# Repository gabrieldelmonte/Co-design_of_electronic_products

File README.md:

# PBLE01 - Electronic Product Co-design Project

## Overview
This repository contains the complete design files and documentation for PBLE01 - Electronic Product Co-design, a university project developed at UNIFEI (Federal University of Itajubá). The project involves designing a custom printed circuit board (PCB) with microcontroller-based functionality, peripheral interfaces, and power management systems.

## Project Features
- **Microcontroller**: STM32F030K6T6TR (ARM Cortex-M0)
- **Power Supply**: 5V via USB-C with voltage regulation to 3.3V
- **Peripherals**:
  - LCD interface (16x2 character display)
  - 3-button tactile keyboard
  - Status LEDs
  - USB-Serial transceiver (MCP2200)
  - EEPROM memory (24LC512)
  - Light sensor (PDV-P8103 photoresistor)
- **Expansion Interfaces**:
  - SPI connector
  - I²C connector
  - General-purpose GPIO pins
- **Programming Interfaces**: SWD and UART
- **Safety Features**:
  - Overcurrent protection (PPTC fuse)
  - Reverse voltage protection
  - Power indication LEDs

## Technical Specifications
| Parameter             | Value               |
|-----------------------|---------------------|
| PCB Dimensions        | 70 × 70 mm          |
| Layer Count           | 2 (double-sided)    |
| Signal Trace Width    | ≥ 8 mils            |
| Power Trace Width     | ≥ 12 mils           |
| Minimum Spacing       | 8 mils              |
| Minimum Via Diameter  | 12 mils             |
| Operating Voltage     | 5V DC (USB powered) |
| Voltage Regulation    | 3.3V (LD1117S33TR)  |
| Microcontroller Clock | 8 MHz crystal       |

## Repository Structure

```
├── Hardware/
│   └── Projeto_2022014552/ # Complete KiCad design files
├── Documentation/
│   ├── Manual.pdf          # Complete technical documentation
│   ├── Design_Guidelines.pdf
│   └── Requirements.pdf
└── Components/
    └── .../                # Components used in the project Kicad
```

## Design Tools
- **PCB Design**: KiCad v8.99
- **Documentation**: LaTeX/Overleaf
- **Simulation**: Not applicable (hardware-only project)

## Key Design Sections
1. **Power Subcircuit**  
   - USB-C input (USB4215-03-A)
   - Voltage regulation (LD1117S33TR)
   - Power indicators (5V/3.3V LEDs)

2. **Operation Subcircuit**  
   - STM32F030K6 microcontroller
   - 8MHz crystal oscillator
   - Boot mode selection

3. **Peripheral Subcircuit**  
   - USB-Serial interface (MCP2200)
   - EEPROM memory (24LC512)
   - Ambient light sensor (PDV-P8103)

4. **Expansion Interfaces**  
   - SPI (4-wire + power)
   - I²C (2-wire + power)
   - GPIO breakout

## Bill of Materials Highlights
| Component       | Qty | Description            |
|-----------------|-----|------------------------|
| STM32F030K6T6TR | 1   | ARM Cortex-M0 MCU      |
| LD1117S33TR     | 1   | 3.3V Voltage Regulator |
| MCP2200-I/SO    | 1   | USB-UART Bridge        |
| 24LC512-I/SN    | 1   | 512KB EEPROM           |
| PDV-P8103       | 1   | Photoresistor          |
| USB4215-03-A    | 1   | USB-C Connector        |
| JHD162A         | 1   | 16×2 LCD Display       |
| 3296W-1-103RLF  | 1   | 10kΩ Trimmer           |

## Design Validation
- Electrical Rule Check (ERC) passed in KiCad
- Design Rule Check (DRC) compliant with course requirements
- Power consumption analysis included
- Component placement optimized for signal integrity

## Academic Context
Developed for **PBLE01 - Electronic Product Co-design** (2024.2 Semester) at UNIFEI under Prof. Rodrigo de Paula Rodrigues. The project fulfills all course requirements specified in the design guidelines documentation.

## License
This project is for academic purposes. Component datasheets remain property of their respective manufacturers. Design files are provided as-is without warranty.

---

> **Note**: This design has NOT been manufactured yet. See project manual for validation reports and design analysis.

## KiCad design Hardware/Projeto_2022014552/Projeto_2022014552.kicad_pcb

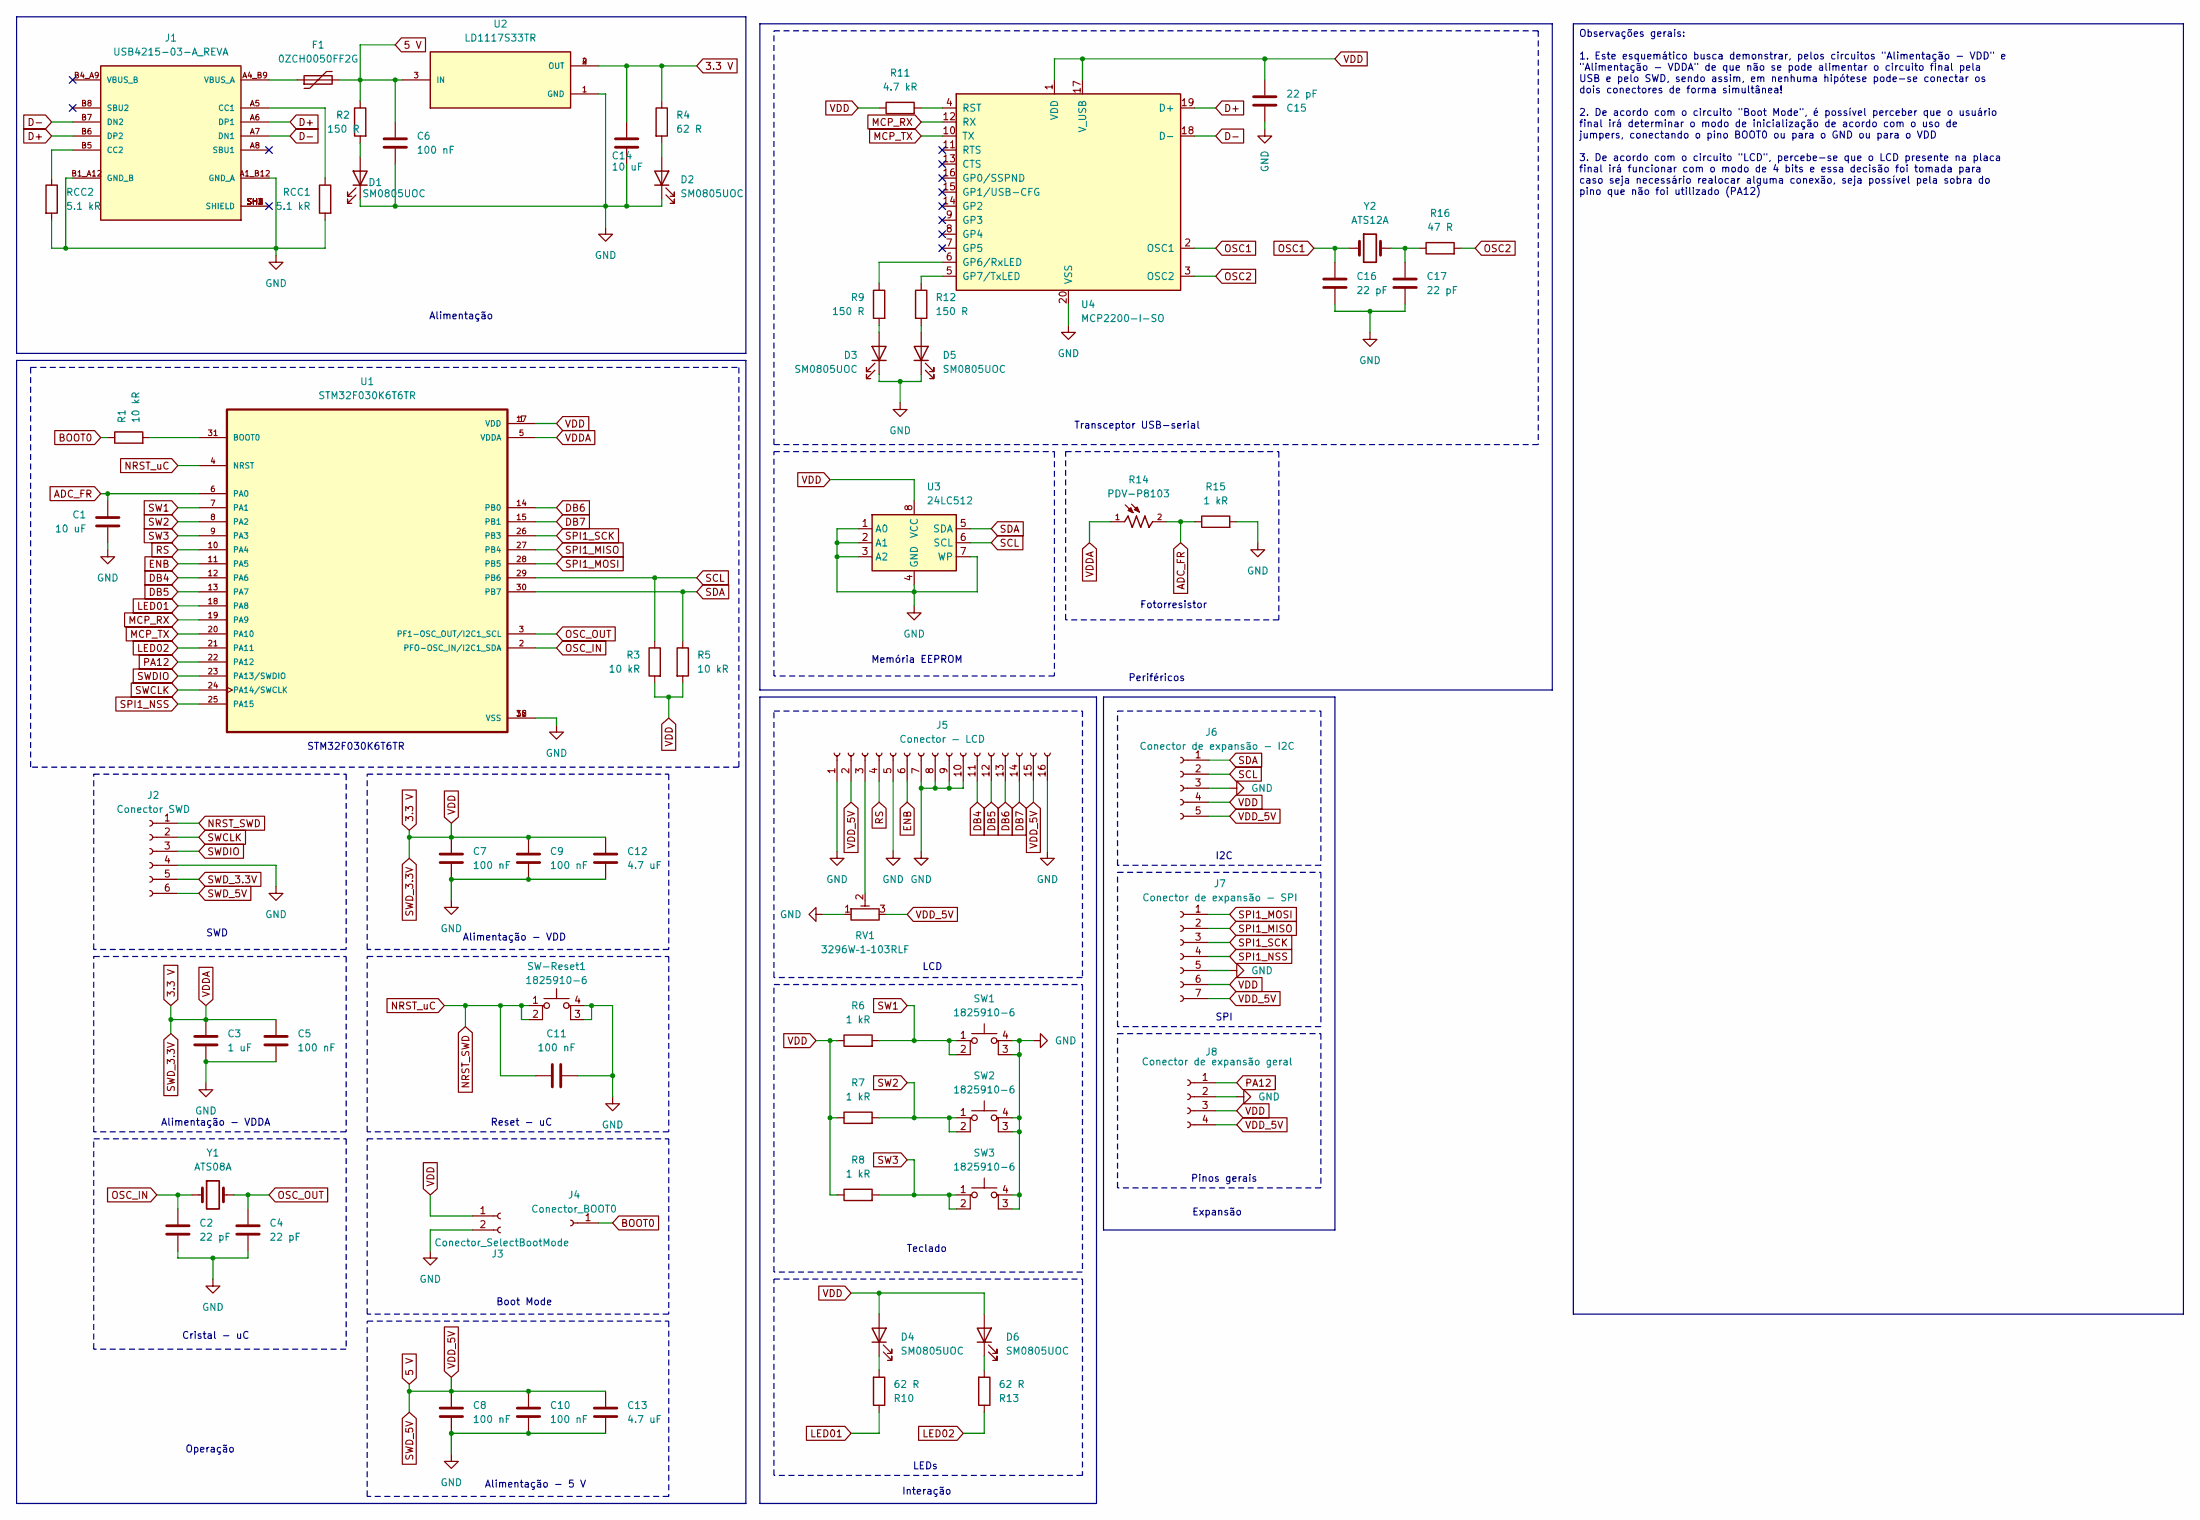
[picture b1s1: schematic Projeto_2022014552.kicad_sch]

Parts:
C1, C14: 10 uF; C_0805_2012Metric
C2, C4, C15, C16, C17: 22 pF; C_0805_2012Metric
C3: 1 uF; C_0805_2012Metric
C5, C6, C7, C8, C9, C10, C11: 100 nF; C_0805_2012Metric
C12, C13: 4.7 uF; C_0805_2012Metric
D1, D2, D3, D4, D5, D6: SM0805UOC
F1: 0ZCH0050FF2G; RESC3225X75N
J1: USB4215-03-A_REVA; GCT_USB4215-03-A_REVA; PARTREV A; DigiKey_Part_Number 2073-USB4215-03-ATR-ND
J2: Conector SWD; PinSocket_1x06_P2.54mm_Vertical
J3: Conector_SelectBootMode; PinSocket_1x02_P2.54mm_Vertical
J4: Conector_BOOT0; PinSocket_1x01_P2.54mm_Vertical
J5: Conector - LCD; PinSocket_1x16_P2.54mm_Vertical
J6: Conector de expansão - I2C; PinSocket_1x05_P2.54mm_Vertical
J7: Conector de expansão - SPI; PinSocket_1x07_P2.54mm_Vertical
J8: Conector de expansão geral; PinSocket_1x04_P2.54mm_Vertical
R1, R3, R5: 10 kR; R_0805_2012Metric
R2, R9, R12: 150 R; R_0805_2012Metric
R4, R10, R13: 62 R; R_0805_2012Metric
R6, R7, R8, R15: 1 kR; R_0805_2012Metric
R11: 4.7 kR; R_0805_2012Metric
R14: PDV-P8103; PHODET_PDV-P8103; PARTREV 3/30/06
R16: 47 R; R_0805_2012Metric
RCC1, RCC2: 5.1 kR; R_0805_2012Metric
RV1: 3296W–1–103RLF; TRIM_3296W-1-103RLF
SW1, SW2, SW3: 1825910-6; SW_1825910-6-4
SW-Reset1: 1825910-6; SW_1825910-6-4
U1: STM32F030K6T6TR; QFP80P900X900X160-32N; PARTREV 3
U2: LD1117S33TR; SOT230P700X180-4N
U3: 24LC512; SOIC127P794X203-8N
U4: MCP2200-I-SO; SOIC20
Y1: ATS08A; XTAL_HC49P488W43L1085T450H368
Y2: ATS12A

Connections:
3.3 V: C3.1, C5.1, C7.1, C9.1, C12.1, C14.2, C15.2, D4.2 (A), D6.2 (A), J2.5, J3.1, J6.4, J7.6, J8.3, R3.2, R4.1, R5.2, R6.1, R7.1, R8.1, R11.1, R14.1, U1.1 (VDD), U1.5 (VDDA), U1.17 (VDD), U2.2 (OUT), U2.4 (OUT), U3.8 (VCC), U4.1 (VDD), U4.17 (V_USB)
5 V: C6.1, C8.1, C10.1, C13.1, F1.2, J2.6, J5.2, J5.15, J6.5, J7.7, J8.4, R2.1, RV1.3, U2.3 (IN)
ADC_FR: C1.1, R14.2, R15.1, U1.6 (PA0)
BOOT0: J4.1, R1.1
D+: J1.A6 (DP1), J1.B6 (DP2), U4.19 (D+)
D-: J1.A7 (DN1), J1.B7 (DN2), U4.18 (D-)
DB4: J5.11, U1.12 (PA6)
DB5: J5.12, U1.13 (PA7)
DB6: J5.13, U1.14 (PB0)
DB7: J5.14, U1.15 (PB1)
ENB: J5.6, U1.11 (PA5)
GND: C1.2, C2.2, C3.2, C4.2, C5.2, C6.2, C7.2, C8.2, C9.2, C10.2, C11.2, C12.2, C13.2, C14.1, C15.1, C16.2, C17.2, D1.1 (K), D2.1 (K), D3.1 (K), D5.1 (K), J1.A1_B12 (GND_A), J1.B1_A12 (GND_B), J2.4, J3.2, J5.1, J5.5, J5.7, J5.8, J5.9, J5.10, J5.16, J6.3, J7.5, J8.2, R15.2, RCC1.2, RCC2.2, RV1.1, SW1.3 (K), SW1.4 (A), SW2.3 (K), SW2.4 (A), SW3.3 (K), SW3.4 (A), SW-Reset1.3 (K), SW-Reset1.4 (A), U1.16 (VSS), U1.32 (VSS), U2.1 (GND), U3.1 (A0), U3.2 (A1), U3.3 (A2), U3.4 (GND), U3.7 (WP), U4.20 (VSS)
LED01: R10.1, U1.18 (PA8)
LED02: R13.1, U1.21 (PA11)
MCP_RX: U1.19 (PA9), U4.12 (RX)
MCP_TX: U1.20 (PA10), U4.10 (TX)
NRST_SWD: C11.1, J2.1, SW-Reset1.1, SW-Reset1.2, U1.4 (NRST)
unnamed: C17.1, R16.1, Y2.2
unnamed: D1.2 (A), R2.2
unnamed: D2.2 (A), R4.2
unnamed: D3.2 (A), R9.2
unnamed: D4.1 (K), R10.2
unnamed: D5.2 (A), R12.2
unnamed: D6.1 (K), R13.2
unnamed: J1.A5 (CC1), RCC1.1
unnamed: J1.B5 (CC2), RCC2.1
unnamed: F1.1, J1.A4_B9 (VBUS_A)
unnamed: J5.3, RV1.2
unnamed: R1.2, U1.31 (BOOT0)
unnamed: R9.1, U4.6 (GP6/RxLED)
unnamed: R12.1, U4.5 (GP7/TxLED)
unnamed: R11.2, U4.4 (RST)
OSC1: C16.1, U4.2 (OSC1), Y2.1
OSC2: R16.2, U4.3 (OSC2)
OSC_IN: C2.1, U1.2 (PFO-OSC_IN/I2C1_SDA), Y1.1
OSC_OUT: C4.1, U1.3 (PF1-OSC_OUT/I2C1_SCL), Y1.2
PA12: J8.1, U1.22 (PA12)
RS: J5.4, U1.10 (PA4)
SCL: J6.2, R3.1, U1.29 (PB6), U3.6 (SCL)
SDA: J6.1, R5.1, U1.30 (PB7), U3.5 (SDA)
SPI1_MISO: J7.2, U1.27 (PB4)
SPI1_MOSI: J7.1, U1.28 (PB5)
SPI1_NSS: J7.4, U1.25 (PA15)
SPI1_SCK: J7.3, U1.26 (PB3)
SW1: R6.2, SW1.1, SW1.2, U1.7 (PA1)
SW2: R7.2, SW2.1, SW2.2, U1.8 (PA2)
SW3: R8.2, SW3.1, SW3.2, U1.9 (PA3)
SWCLK: J2.2, U1.24 (PA14/SWCLK)
SWDIO: J2.3, U1.23 (PA13/SWDIO)

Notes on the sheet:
SPI
Expansão
Alimentação - VDDA
Memória EEPROM
Boot Mode
Alimentação
Operação
Interação
Pinos gerais
Transceptor USB-serial
Teclado
STM32F030K6T6TR
I2C
Fotorresistor
Cristal - uC
Periféricos
LEDs
Reset - uC
Alimentação - 5 V
SWD
LCD
Alimentação - VDD
Observações gerais: 1. Este esquemático busca demonstrar, pelos circuitos "Alimentação - VDD" e "Alimentação - VDDA" de que não se pode alimentar o circuito final pela USB e pelo SWD, sendo assim, em nenhuma hipótese pode-se conectar os dois conectores de forma simultânea! 2. De acordo com o circui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

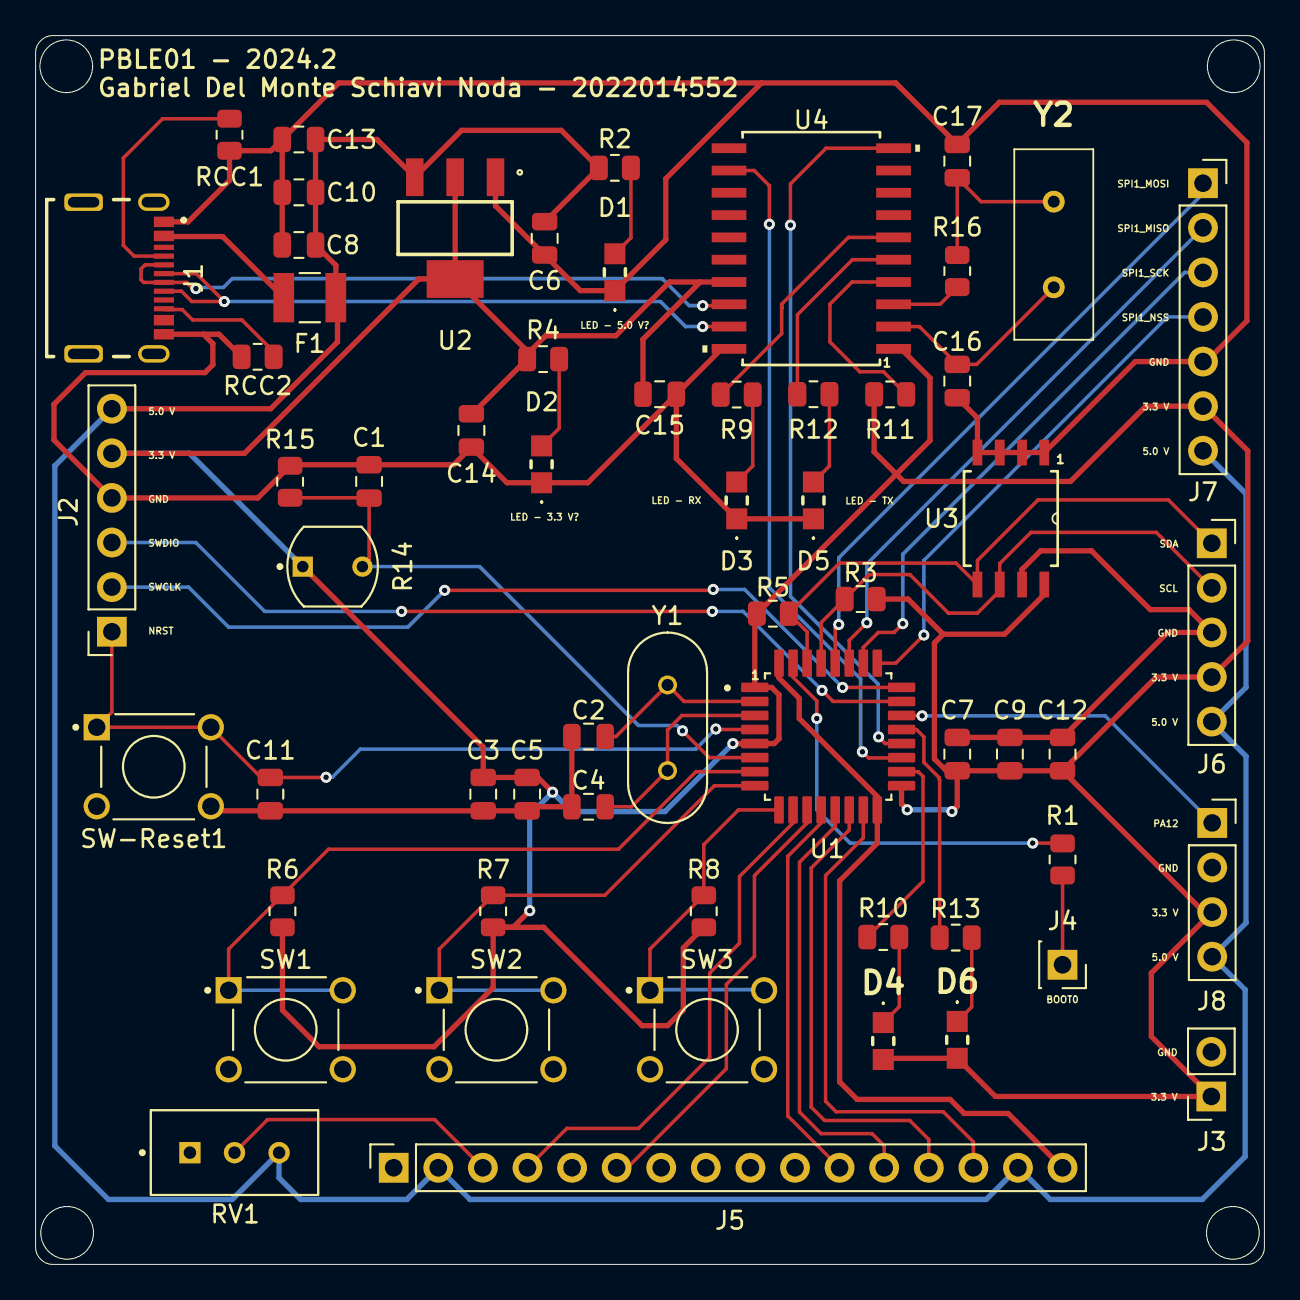
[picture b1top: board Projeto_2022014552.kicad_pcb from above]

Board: 2 copper layers, 70.0 x 70.0 mm, 61 parts (0 on the bottom side), 49 nets.

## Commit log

2025-06-08 Project
